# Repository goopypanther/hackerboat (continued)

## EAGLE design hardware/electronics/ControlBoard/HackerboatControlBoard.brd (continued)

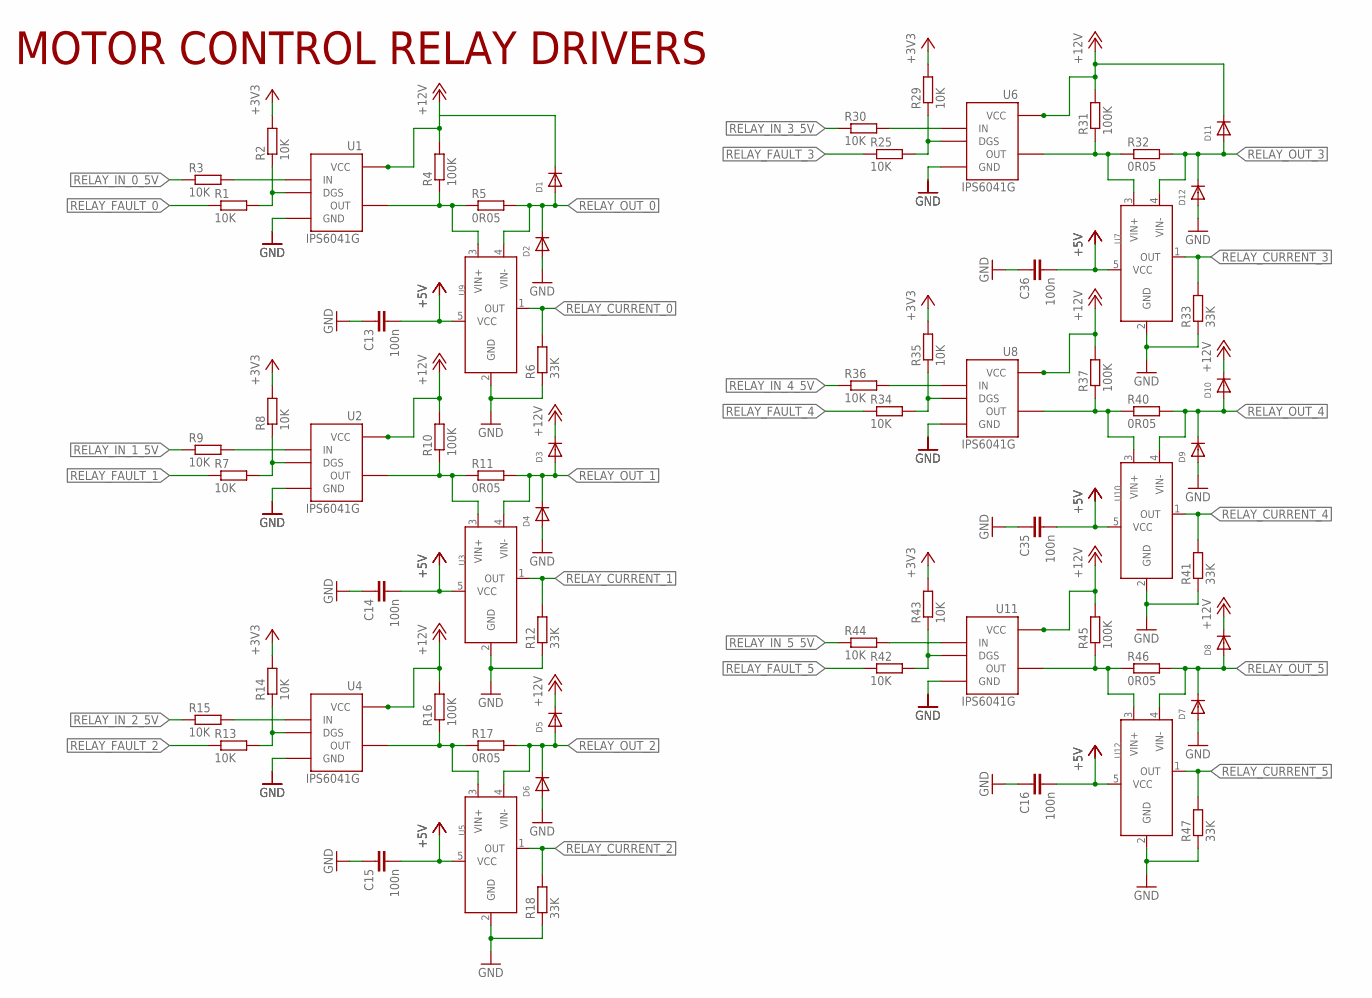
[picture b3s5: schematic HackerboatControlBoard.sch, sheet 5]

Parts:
C13, C14, C15, C16, C35, C36: 100n; C0603; PARTNO CC0603KRX7R9BB104
D1, D2, D3, D4, D5, D6, D7, D8, D9, D10, D11, D12: DIODESOD-123; SOD-123; PARTNO CDBW140-G
R1, R2, R3, R7, R8, R9, R13, R14, R15, R25, R29, R30, R34, R35, R36, R42, R43, R44: 10K; R0603; PARTNO RNCP0603FTD10K0
R4, R10, R16, R31, R37, R45: 100K; R0603; PARTNO CRCW0603100KFKEA
R5, R11, R17, R32, R40, R46: 0R05; R2512; PARTNO PE2512FKE070R05L
R6, R12, R18, R33, R41, R47: 33K; R0603; PARTNO ERJ-3EKF3302V
U1, U2, U4, U6, U8, U11: IPS6041G; SO08; PARTNO IPS6041GPBF
U3, U5, U7, U9, U10, U12: INA169; SOT23-5L; PARTNO INA169NA/3K

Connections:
+3V3: R2.2, R8.2, R14.2, R29.2, R35.2, R43.2; also elsewhere on the board
+5V: C13.2, C14.2, C15.2, C16.2, C35.2, C36.2, U3.5 (VCC), U5.5 (VCC), U7.5 (VCC), U9.5 (VCC), U10.5 (VCC), U12.5 (VCC); also elsewhere on the board
+12V: D1.C, D3.C, D5.C, D8.C, D10.C, D11.C, R4.2, R10.2, R16.2, R31.2, R37.2, R45.2, U1.5 (VCC), U1.6 (VCC), U1.7 (VCC), U1.8 (VCC), U2.5 (VCC), U2.6 (VCC), U2.7 (VCC), U2.8 (VCC), U4.5 (VCC), U4.6 (VCC), U4.7 (VCC), U4.8 (VCC), U6.5 (VCC), U6.6 (VCC), U6.7 (VCC), U6.8 (VCC), U8.5 (VCC), U8.6 (VCC), U8.7 (VCC), U8.8 (VCC), U11.5 (VCC), U11.6 (VCC), U11.7 (VCC), U11.8 (VCC); also elsewhere on the board
GND: C13.1, C14.1, C15.1, C16.1, C35.1, C36.1, D2.A, D4.A, D6.A, D7.A, D9.A, D12.A, R6.1, R12.1, R18.1, R33.1, R41.1, R47.1, U1.1 (GND), U2.1 (GND), U3.2 (GND), U4.1 (GND), U5.2 (GND), U6.1 (GND), U7.2 (GND), U8.1 (GND), U9.2 (GND), U10.2 (GND), U11.1 (GND), U12.2 (GND); also elsewhere on the board
unnamed: R1.2, R2.1, U1.3 (DGS)
unnamed: R3.2, U1.2 (IN)
unnamed: R4.1, R5.1, U1.4 (OUT), U9.3 (VIN+)
unnamed: R7.2, R8.1, U2.3 (DGS)
unnamed: R9.2, U2.2 (IN)
unnamed: R10.1, R11.1, U2.4 (OUT), U3.3 (VIN+)
unnamed: R13.2, R14.1, U4.3 (DGS)
unnamed: R15.2, U4.2 (IN)
unnamed: R16.1, R17.1, U4.4 (OUT), U5.3 (VIN+)
unnamed: R25.2, R29.1, U6.3 (DGS)
unnamed: R30.2, U6.2 (IN)
unnamed: R31.1, R32.1, U6.4 (OUT), U7.3 (VIN+)
unnamed: R34.2, R35.1, U8.3 (DGS)
unnamed: R36.2, U8.2 (IN)
unnamed: R37.1, R40.1, U8.4 (OUT), U10.3 (VIN+)
unnamed: R42.2, R43.1, U11.3 (DGS)
unnamed: R44.2, U11.2 (IN)
unnamed: R45.1, R46.1, U11.4 (OUT), U12.3 (VIN+)
RELAY_CURRENT_0: R6.2, U9.1 (OUT); also elsewhere on the board
RELAY_CURRENT_1: R12.2, U3.1 (OUT); also elsewhere on the board
RELAY_CURRENT_2: R18.2, U5.1 (OUT); also elsewhere on the board
RELAY_CURRENT_3: R33.2, U7.1 (OUT); also elsewhere on the board
RELAY_CURRENT_4: R41.2, U10.1 (OUT); also elsewhere on the board
RELAY_CURRENT_5: R47.2, U12.1 (OUT); also elsewhere on the board
RELAY_FAULT_0: R1.1; also elsewhere on the board
RELAY_FAULT_1: R7.1; also elsewhere on the board
RELAY_FAULT_2: R13.1; also elsewhere on the board
RELAY_FAULT_3: R25.1; also elsewhere on the board
RELAY_FAULT_4: R34.1; also elsewhere on the board
RELAY_FAULT_5: R42.1; also elsewhere on the board
RELAY_IN_0_5V: R3.1; also elsewhere on the board
RELAY_IN_1_5V: R9.1; also elsewhere on the board
RELAY_IN_2_5V: R15.1; also elsewhere on the board
RELAY_IN_3_5V: R30.1; also elsewhere on the board
RELAY_IN_4_5V: R36.1; also elsewhere on the board
RELAY_IN_5_5V: R44.1; also elsewhere on the board
RELAY_OUT_0: D1.A, D2.C, R5.2, U9.4 (VIN-); also elsewhere on the board
RELAY_OUT_1: D3.A, D4.C, R11.2, U3.4 (VIN-); also elsewhere on the board
RELAY_OUT_2: D5.A, D6.C, R17.2, U5.4 (VIN-); also elsewhere on the board
RELAY_OUT_3: D11.A, D12.C, R32.2, U7.4 (VIN-); also elsewhere on the board
RELAY_OUT_4: D9.C, D10.A, R40.2, U10.4 (VIN-); also elsewhere on the board
RELAY_OUT_5: D7.C, D8.A, R46.2, U12.4 (VIN-); also elsewhere on the board

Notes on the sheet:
MOTOR CONTROL RELAY DRIVERS

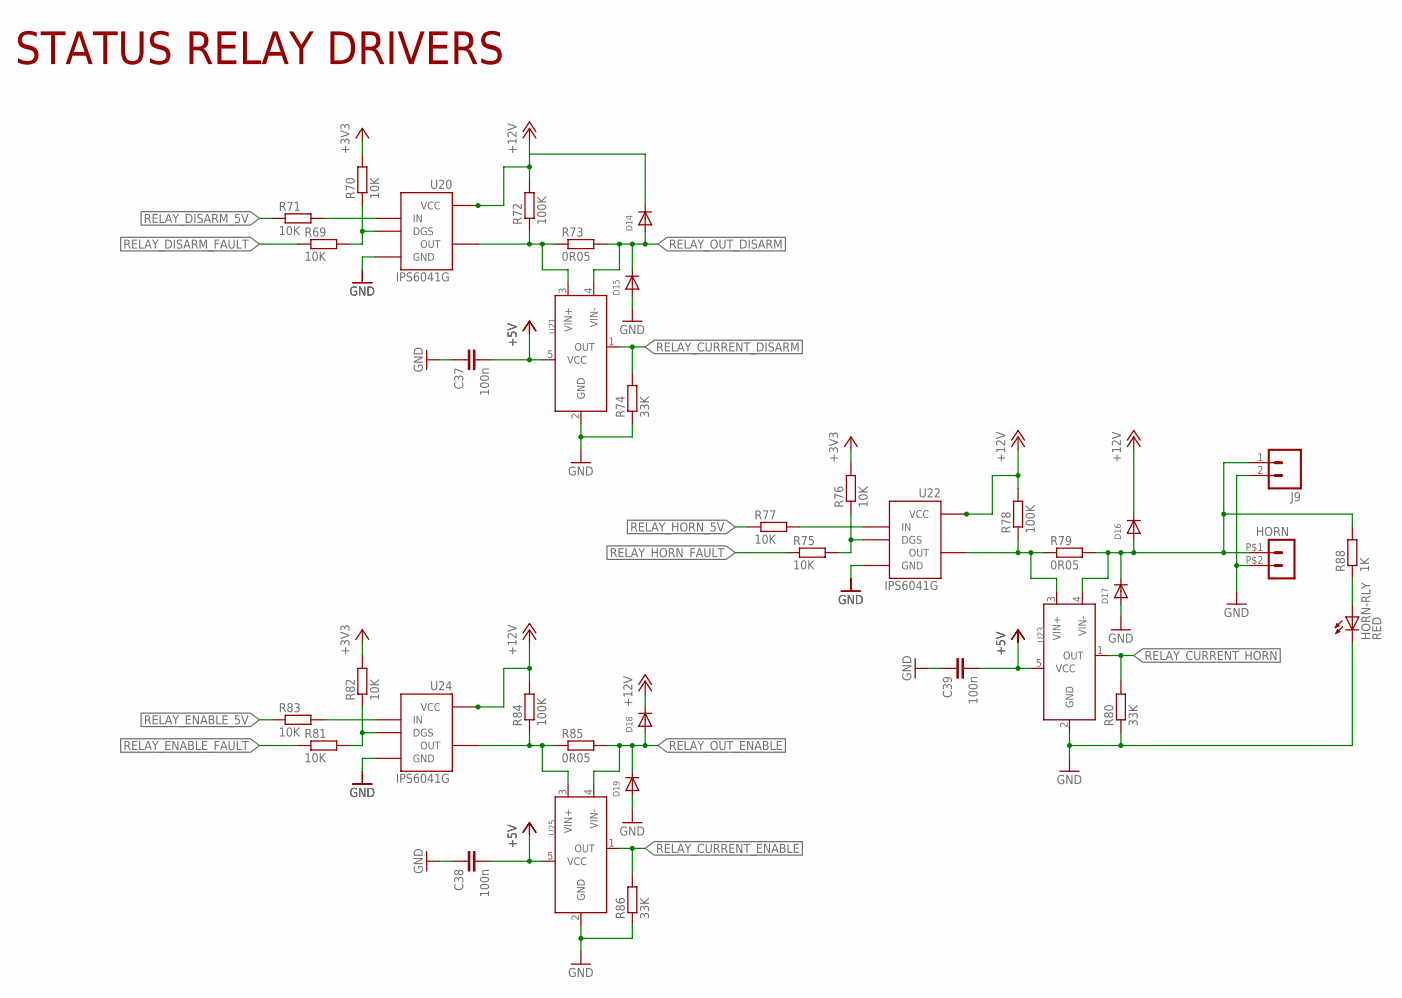
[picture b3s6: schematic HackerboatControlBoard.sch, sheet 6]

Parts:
C37, C38, C39: 100n; C0603; PARTNO CC0603KRX7R9BB104
D14, D15, D16, D17, D18, D19: DIODESOD-123; SOD-123; PARTNO CDBW140-G
HORN: HEADER_POS2_70555; 70555-POS2; PARTNO 0705550036
HORN-RLY: RED; CHIPLED_0805; PARTNO LH R974-LP-1
J9: M02LOCK; 1X02_LOCK; PARTNO ?
R69, R70, R71, R75, R76, R77, R81, R82, R83: 10K; R0603; PARTNO RNCP0603FTD10K0
R72, R78, R84: 100K; R0603; PARTNO CRCW0603100KFKEA
R73, R79, R85: 0R05; R2512; PARTNO PE2512FKE070R05L
R74, R80, R86: 33K; R0603; PARTNO ERJ-3EKF3302V
R88: 1K; R0603; PARTNO RMCF0603FT1K00
U20, U22, U24: IPS6041G; SO08; PARTNO IPS6041GPBF
U21, U23, U25: INA169; SOT23-5L; PARTNO INA169NA/3K

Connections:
+3V3: R70.2, R76.2, R82.2; also elsewhere on the board
+5V: C37.2, C38.2, C39.2, U21.5 (VCC), U23.5 (VCC), U25.5 (VCC); also elsewhere on the board
+12V: D14.C, D16.C, D18.C, R72.2, R78.2, R84.2, U20.5 (VCC), U20.6 (VCC), U20.7 (VCC), U20.8 (VCC), U22.5 (VCC), U22.6 (VCC), U22.7 (VCC), U22.8 (VCC), U24.5 (VCC), U24.6 (VCC), U24.7 (VCC), U24.8 (VCC); also elsewhere on the board
GND: C37.1, C38.1, C39.1, D15.A, D17.A, D19.A, HORN.P$2 (2), HORN-RLY.C, J9.2, R74.1, R80.1, R86.1, U20.1 (GND), U21.2 (GND), U22.1 (GND), U23.2 (GND), U24.1 (GND), U25.2 (GND); also elsewhere on the board
unnamed: R69.2, R70.1, U20.3 (DGS)
unnamed: R71.2, U20.2 (IN)
unnamed: R72.1, R73.1, U20.4 (OUT), U21.3 (VIN+)
unnamed: R75.2, R76.1, U22.3 (DGS)
unnamed: R77.2, U22.2 (IN)
unnamed: R78.1, R79.1, U22.4 (OUT), U23.3 (VIN+)
unnamed: R81.2, R82.1, U24.3 (DGS)
unnamed: R83.2, U24.2 (IN)
unnamed: R84.1, R85.1, U24.4 (OUT), U25.3 (VIN+)
unnamed: HORN-RLY.A, R88.1
RELAY_CURRENT_DISARM: R74.2, U21.1 (OUT); also elsewhere on the board
RELAY_CURRENT_ENABLE: R86.2, U25.1 (OUT); also elsewhere on the board
RELAY_CURRENT_HORN: R80.2, U23.1 (OUT); also elsewhere on the board
RELAY_DISARM_5V: R71.1; also elsewhere on the board
RELAY_DISARM_FAULT: R69.1; also elsewhere on the board
RELAY_ENABLE_5V: R83.1; also elsewhere on the board
RELAY_ENABLE_FAULT: R81.1; also elsewhere on the board
RELAY_HORN_5V: R77.1; also elsewhere on the board
RELAY_HORN_FAULT: R75.1; also elsewhere on the board
RELAY_OUT_DISARM: D14.A, D15.C, R73.2, U21.4 (VIN-); also elsewhere on the board
RELAY_OUT_ENABLE: D18.A, D19.C, R85.2, U25.4 (VIN-); also elsewhere on the board
RELAY_OUT_HORN: D16.A, D17.C, HORN.P$1 (1), J9.1, R79.2, R88.2, U23.4 (VIN-)

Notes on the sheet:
STATUS RELAY DRIVERS

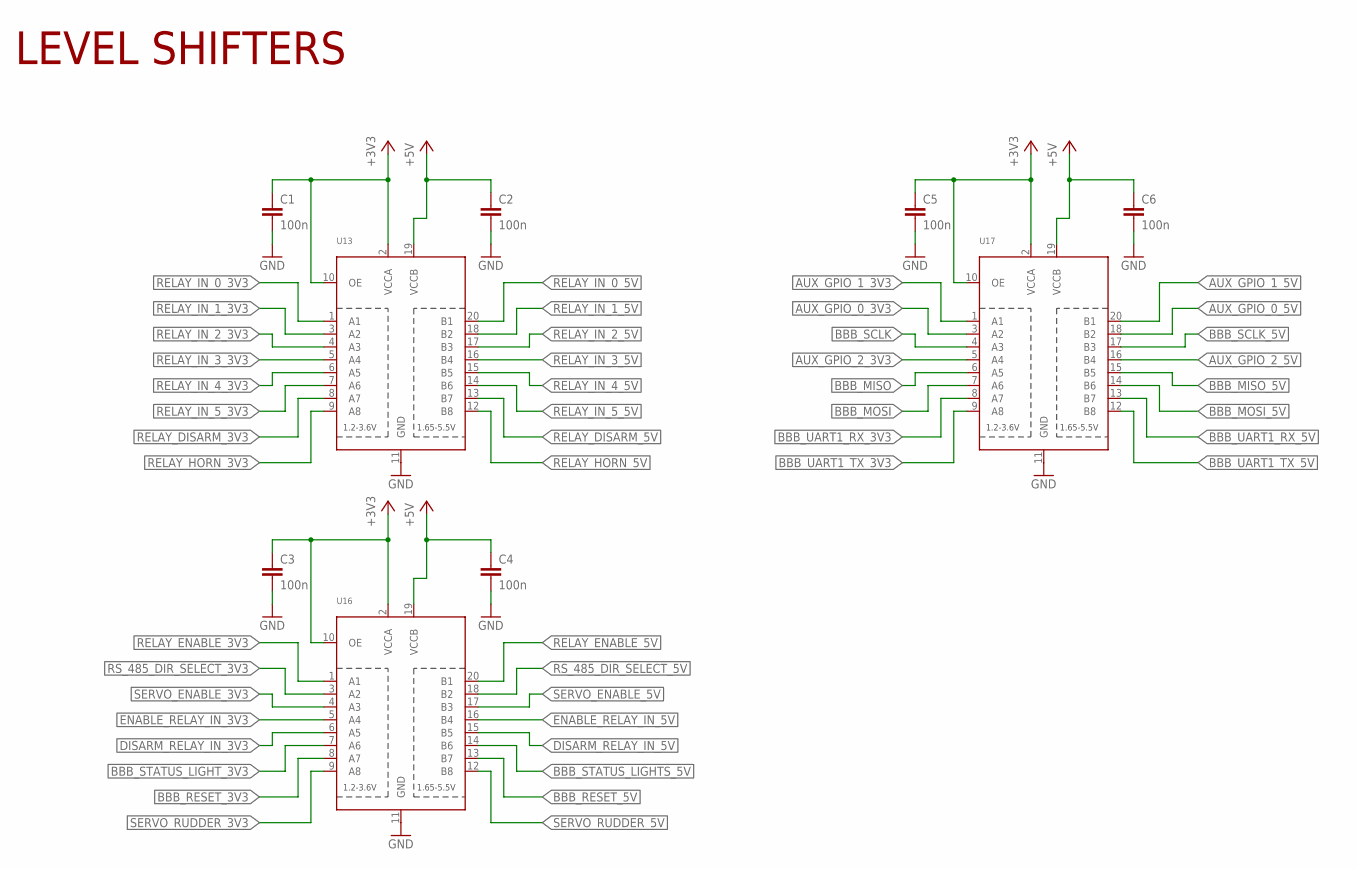
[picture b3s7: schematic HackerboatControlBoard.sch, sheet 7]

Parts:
C1, C2, C3, C4, C5, C6: 100n; C0603; PARTNO CC0603KRX7R9BB104
U13, U16, U17: TXB0108PWR; TSSOP20; PARTNO TXB0108PWR

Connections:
+3V3: C1.1, C3.1, C5.1, U13.2 (VCCA), U13.10 (OE), U16.2 (VCCA), U16.10 (OE), U17.2 (VCCA), U17.10 (OE); also elsewhere on the board
+5V: C2.1, C4.1, C6.1, U13.19 (VCCB), U16.19 (VCCB), U17.19 (VCCB); also elsewhere on the board
AUX_GPIO_0_3V3: U17.3 (A2); also elsewhere on the board
AUX_GPIO_0_5V: U17.18 (B2); also elsewhere on the board
AUX_GPIO_1_3V3: U17.1 (A1); also elsewhere on the board
AUX_GPIO_1_5V: U17.20 (B1); also elsewhere on the board
AUX_GPIO_2_3V3: U17.5 (A4); also elsewhere on the board
AUX_GPIO_2_5V: U17.16 (B4); also elsewhere on the board
BBB_MISO: U17.6 (A5); also elsewhere on the board
BBB_MISO_5V: U17.15 (B5); also elsewhere on the board
BBB_MOSI: U17.7 (A6); also elsewhere on the board
BBB_MOSI_5V: U17.14 (B6); also elsewhere on the board
BBB_RESET_3V3: U16.8 (A7); also elsewhere on the board
BBB_RESET_5V: U16.13 (B7); also elsewhere on the board
BBB_SCLK: U17.4 (A3); also elsewhere on the board
BBB_SCLK_5V: U17.17 (B3); also elsewhere on the board
BBB_STATUS_LIGHTS_5V: U16.14 (B6); also elsewhere on the board
BBB_STATUS_LIGHT_3V3: U16.7 (A6)
BBB_UART1_RX_3V3: U17.8 (A7); also elsewhere on the board
BBB_UART1_RX_5V: U17.13 (B7); also elsewhere on the board
BBB_UART1_TX_3V3: U17.9 (A8); also elsewhere on the board
BBB_UART1_TX_5V: U17.12 (B8); also elsewhere on the board
DISARM_RELAY_IN_3V3: U16.6 (A5); also elsewhere on the board
DISARM_RELAY_IN_5V: U16.15 (B5); also elsewhere on the board
ENABLE_RELAY_IN_3V3: U16.5 (A4); also elsewhere on the board
ENABLE_RELAY_IN_5V: U16.16 (B4); also elsewhere on the board
GND: C1.2, C2.2, C3.2, C4.2, C5.2, C6.2, U13.11 (GND), U16.11 (GND), U17.11 (GND); also elsewhere on the board
RELAY_DISARM_3V3: U13.8 (A7); also elsewhere on the board
RELAY_DISARM_5V: U13.13 (B7); also elsewhere on the board
RELAY_ENABLE_3V3: U16.1 (A1); also elsewhere on the board
RELAY_ENABLE_5V: U16.20 (B1); also elsewhere on the board
RELAY_HORN_3V3: U13.9 (A8); also elsewhere on the board
RELAY_HORN_5V: U13.12 (B8); also elsewhere on the board
RELAY_IN_0_3V3: U13.1 (A1); also elsewhere on the board
RELAY_IN_0_5V: U13.20 (B1); also elsewhere on the board
RELAY_IN_1_3V3: U13.3 (A2); also elsewhere on the board
RELAY_IN_1_5V: U13.18 (B2); also elsewhere on the board
RELAY_IN_2_3V3: U13.4 (A3); also elsewhere on the board
RELAY_IN_2_5V: U13.17 (B3); also elsewhere on the board
RELAY_IN_3_3V3: U13.5 (A4); also elsewhere on the board
RELAY_IN_3_5V: U13.16 (B4); also elsewhere on the board
RELAY_IN_4_3V3: U13.6 (A5); also elsewhere on the board
RELAY_IN_4_5V: U13.15 (B5); also elsewhere on the board
RELAY_IN_5_3V3: U13.7 (A6); also elsewhere on the board
RELAY_IN_5_5V: U13.14 (B6); also elsewhere on the board
RS_485_DIR_SELECT_3V3: U16.3 (A2); also elsewhere on the board
RS_485_DIR_SELECT_5V: U16.18 (B2); also elsewhere on the board
SERVO_ENABLE_3V3: U16.4 (A3); also elsewhere on the board
SERVO_ENABLE_5V: U16.17 (B3); also elsewhere on the board
SERVO_RUDDER_3V3: U16.9 (A8); also elsewhere on the board
SERVO_RUDDER_5V: U16.12 (B8); also elsewhere on the board

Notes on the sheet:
LEVEL SHIFTERS

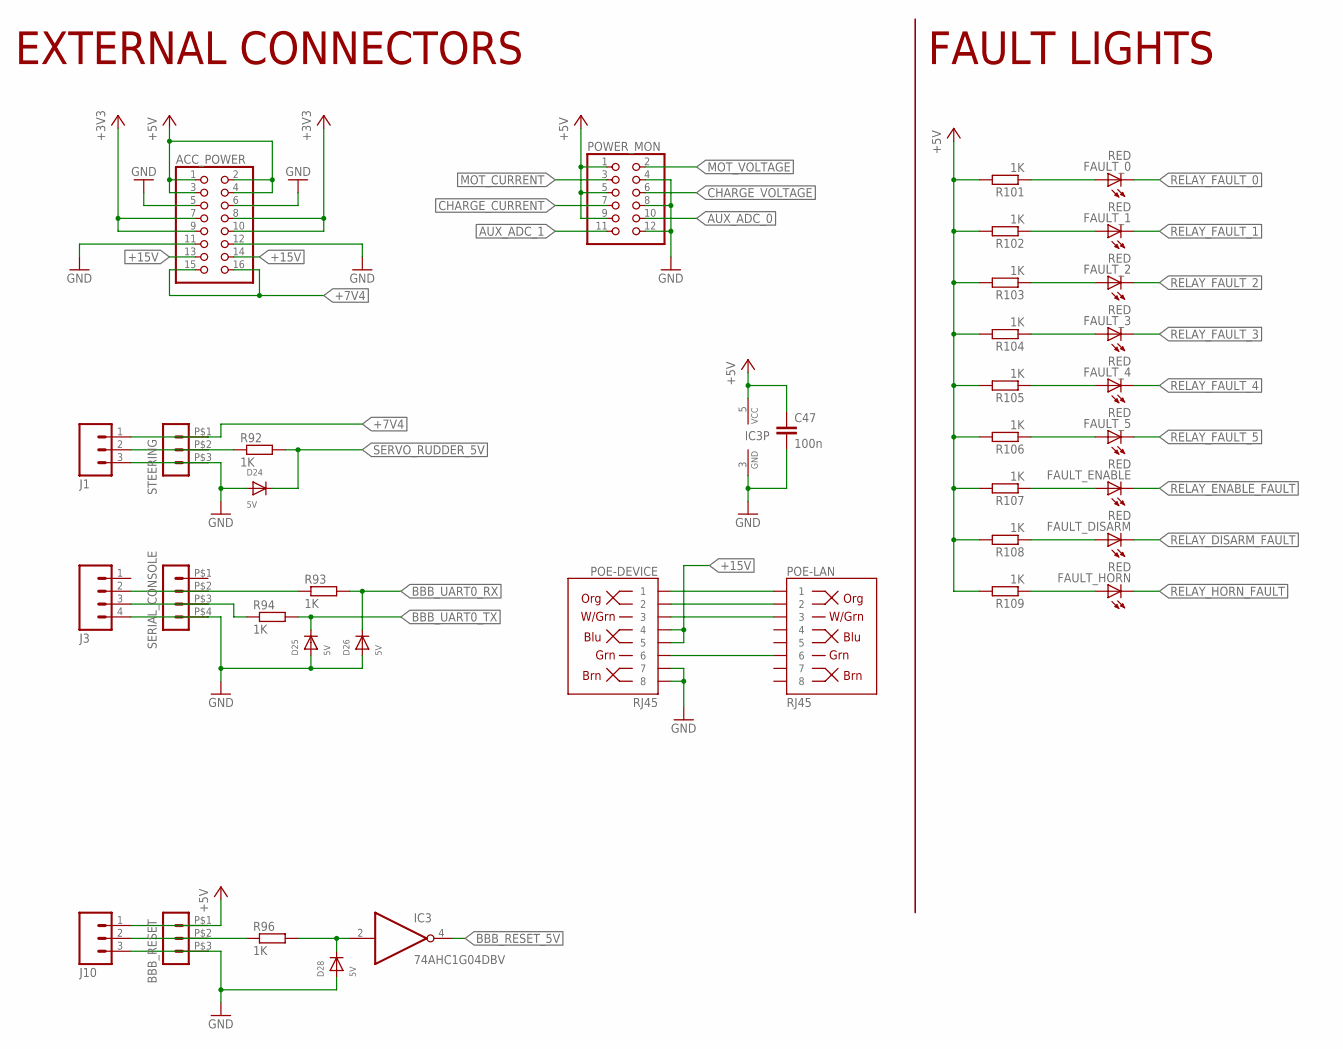
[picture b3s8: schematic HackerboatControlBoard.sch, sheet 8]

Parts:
ACC_POWER: PINHD-2X8_2.54; 2X08; PARTNO *
BBB_RESET: HEADER_POS3_70555; 70555-POS3; PARTNO 0705550037
C47: 100n; C0603; PARTNO CC0603KRX7R9BB104
D24, D25, D26, D28: 5V; SOD-123; PARTNO SMF5.0A
FAULT_0, FAULT_1, FAULT_2, FAULT_3, FAULT_4, FAULT_5: RED; CHIPLED_0805; PARTNO LH R974-LP-1
FAULT_DISARM: RED; CHIPLED_0805; PARTNO LH R974-LP-1
FAULT_ENABLE: RED; CHIPLED_0805; PARTNO LH R974-LP-1
FAULT_HORN: RED; CHIPLED_0805; PARTNO LH R974-LP-1
IC3: 74AHC1G04DBV; SOT23-5; PARTNO MC74HC1G04DTT1G
J1, J10: M03LOCK; 1X03_LOCK; PARTNO ?
J3: M04LOCK; 1X04_LOCK; PARTNO *
POE-DEVICE: RJ45; RJ45-8; PARTNO 615008137121
POE-LAN: RJ45; RJ45-8; PARTNO 615008137121
POWER_MON: PINHD-2X6_2.54; 2X06; PARTNO *
R92, R93, R94, R96, R101, R102, R103, R104, R105, R106, R107, R108, R109: 1K; R0603; PARTNO RMCF0603FT1K00
SERIAL_CONSOLE: HEADER_POS4_70555; 70555-POS4; PARTNO 0705550038
STEERING: HEADER_POS3_70555; 70555-POS3; PARTNO 0705550037

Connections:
+3V3: ACC_POWER.7, ACC_POWER.8, ACC_POWER.9, ACC_POWER.10; also elsewhere on the board
+5V: ACC_POWER.1, ACC_POWER.2, ACC_POWER.3, ACC_POWER.4, BBB_RESET.P$1 (1), C47.1, IC3.5 (VCC), J10.1, POWER_MON.1, POWER_MON.5, POWER_MON.9, R101.2, R102.2, R103.2, R104.2, R105.2, R106.2, R107.2, R108.2, R109.2; also elsewhere on the board
+7V4: ACC_POWER.15, ACC_POWER.16, J1.1, STEERING.P$1 (1); also elsewhere on the board
+15V: ACC_POWER.13, ACC_POWER.14, POE-DEVICE.4, POE-DEVICE.5; also elsewhere on the board
AUX_ADC_0: POWER_MON.10; also elsewhere on the board
AUX_ADC_1: POWER_MON.11; also elsewhere on the board
BBB_RESET_5V: IC3.4 (O); also elsewhere on the board
BBB_UART0_RX: D26.C, R93.2; also elsewhere on the board
BBB_UART0_TX: D25.C, R94.2; also elsewhere on the board
CHARGE_CURRENT: POWER_MON.7; also elsewhere on the board
CHARGE_VOLTAGE: POWER_MON.6; also elsewhere on the board
GND: ACC_POWER.5, ACC_POWER.6, ACC_POWER.11, ACC_POWER.12, BBB_RESET.P$3 (3), C47.2, D24.A, D25.A, D26.A, D28.A, IC3.3 (GND), J1.3, J3.4, J10.3, POE-DEVICE.7, POE-DEVICE.8, POWER_MON.4, POWER_MON.8, POWER_MON.12, SERIAL_CONSOLE.P$4 (4), STEERING.P$3 (3); also elsewhere on the board
MOT_CURRENT: POWER_MON.3; also elsewhere on the board
MOT_VOLTAGE: POWER_MON.2; also elsewhere on the board
unnamed: D28.C, IC3.2 (I), R96.2
unnamed: POE-DEVICE.1, POE-LAN.1
unnamed: POE-DEVICE.2, POE-LAN.2
unnamed: POE-DEVICE.3, POE-LAN.3
unnamed: POE-DEVICE.6, POE-LAN.6
unnamed: J1.2, R92.1, STEERING.P$2 (2)
unnamed: J3.2, R93.1, SERIAL_CONSOLE.P$2 (2)
unnamed: J3.3, R94.1, SERIAL_CONSOLE.P$3 (3)
unnamed: BBB_RESET.P$2 (2), J10.2, R96.1
unnamed: FAULT_0.A, R101.1
unnamed: FAULT_1.A, R102.1
unnamed: FAULT_2.A, R103.1
unnamed: FAULT_3.A, R104.1
unnamed: FAULT_4.A, R105.1
unnamed: FAULT_5.A, R106.1
unnamed: FAULT_ENABLE.A, R107.1
unnamed: FAULT_DISARM.A, R108.1
unnamed: FAULT_HORN.A, R109.1
RELAY_DISARM_FAULT: FAULT_DISARM.C; also elsewhere on the board
RELAY_ENABLE_FAULT: FAULT_ENABLE.C; also elsewhere on the board
RELAY_FAULT_0: FAULT_0.C; also elsewhere on the board
RELAY_FAULT_1: FAULT_1.C; also elsewhere on the board
RELAY_FAULT_2: FAULT_2.C; also elsewhere on the board
RELAY_FAULT_3: FAULT_3.C; also elsewhere on the board
RELAY_FAULT_4: FAULT_4.C; also elsewhere on the board
RELAY_FAULT_5: FAULT_5.C; also elsewhere on the board
RELAY_HORN_FAULT: FAULT_HORN.C; also elsewhere on the board
SERVO_RUDDER_5V: D24.C, R92.2; also elsewhere on the board

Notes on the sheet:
EXTERNAL CONNECTORS
FAULT LIGHTS

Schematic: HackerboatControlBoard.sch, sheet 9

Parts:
C19: 10u; C1210; PARTNO UMK325BJ106MM
C20: 22u; C1210; PARTNO GRM32ER61E226KE15K
CELL: FONA; FONA-3G; PARTNO BCS-118-L-S-TE
D27: 5V; SOD-123; PARTNO SMF5.0A
F2: PTC-2920; 2920L; PARTNO MF-LSMF300/24X-2
GPS: ULTIMATE-GPS; PARTNO BCS-109-L-S-TE
IC5: V7805-2000; TO220V; PARTNO V7805-2000
IMU: 9-DOF-BREAKOUT; PARTNO BCS-110-L-S-TE
J2: M03LOCK; 1X03_LOCK; PARTNO ?
J5: M09LOCK; 1X09_LOCK; PARTNO *
J6: M10LOCK; 1X10_LOCK; PARTNO *
J7: M18_; 1X18; PARTNO *
R19: 4K7'; R0603; PARTNO RC1608J472CS
R20: 4K7; R0603; PARTNO RC1608J472CS
R95: 1K; R0603; PARTNO RMCF0603FT1K00
STATUS_LIGHTS: HEADER_POS3_70555; 70555-POS3; PARTNO 0705550037

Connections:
+3V3: CELL.VIO (15), J7.15, R19.2, R20.2; also elsewhere on the board
+5V: CELL.5V (18), GPS.VIN (5), IMU.VIN (1), J5.2, J6.1, J7.18; also elsewhere on the board
+12V: C19.1, IC5.1 (VI); also elsewhere on the board
BBB_I2C_1_SCL: IMU.SCL (4), J6.4, R19.1; also elsewhere on the board
BBB_I2C_1_SDA: IMU.SDA (5), J6.5, R20.1; also elsewhere on the board
BBB_STATUS_LIGHTS_5V: D27.C, R95.2; also elsewhere on the board
CELL_CTS: CELL.CTS (9), J7.9; also elsewhere on the board
CELL_KEY: CELL.KEY (8), J7.8; also elsewhere on the board
CELL_NET_STATUS: CELL.NS (5), J7.5; also elsewhere on the board
CELL_POWER_STATUS: CELL.PS (6), J7.6; also elsewhere on the board
CELL_RESET: CELL.RST (14), J7.14; also elsewhere on the board
CELL_RING: CELL.RI (7), J7.7; also elsewhere on the board
CELL_RTS: CELL.RTS (11), J7.11; also elsewhere on the board
CELL_RX: CELL.RX (13), J7.13; also elsewhere on the board
CELL_TX: CELL.TX (12), J7.12; also elsewhere on the board
GND: C19.2, C20.2, CELL.GND (16), D27.A, GPS.GND (6), IC5.2 (GND), IMU.GND (3), J2.3, J5.3, J6.3, J7.16, STATUS_LIGHTS.P$3 (3); also elsewhere on the board
GNSS_ENABLE: GPS.EN (8), J5.8; also elsewhere on the board
GNSS_FIX: GPS.FIX (7), J5.6; also elsewhere on the board
GNSS_RX: GPS.RX (2), J5.4; also elsewhere on the board
GNSS_TX: GPS.TX (3), J5.5; also elsewhere on the board
unnamed: GPS.PPS (1), J5.1
unnamed: GPS.VBAT (4), J5.7
unnamed: IMU.3VO (2), J6.2
unnamed: IMU.GINT (6), J6.6
unnamed: IMU.GRDY (7), J6.7
unnamed: IMU.LIN1 (8), J6.8
unnamed: IMU.LIN2 (9), J6.9
unnamed: IMU.LRDY (10), J6.10
unnamed: GPS.3V3 (9), J5.9
unnamed: CELL.SPKR+ (2), J7.2
unnamed: CELL.MIC- (3), J7.3
unnamed: CELL.MIC+ (4), J7.4
unnamed: CELL.DTR (10), J7.10
unnamed: CELL.BAT (17), J7.17
unnamed: CELL.SPKR- (1), J7.1
unnamed: F2.P$1 (1), J2.1, STATUS_LIGHTS.P$1 (1)
unnamed: C20.1, F2.P$2 (2), IC5.3 (VO)
unnamed: J2.2, R95.1, STATUS_LIGHTS.P$2 (2)

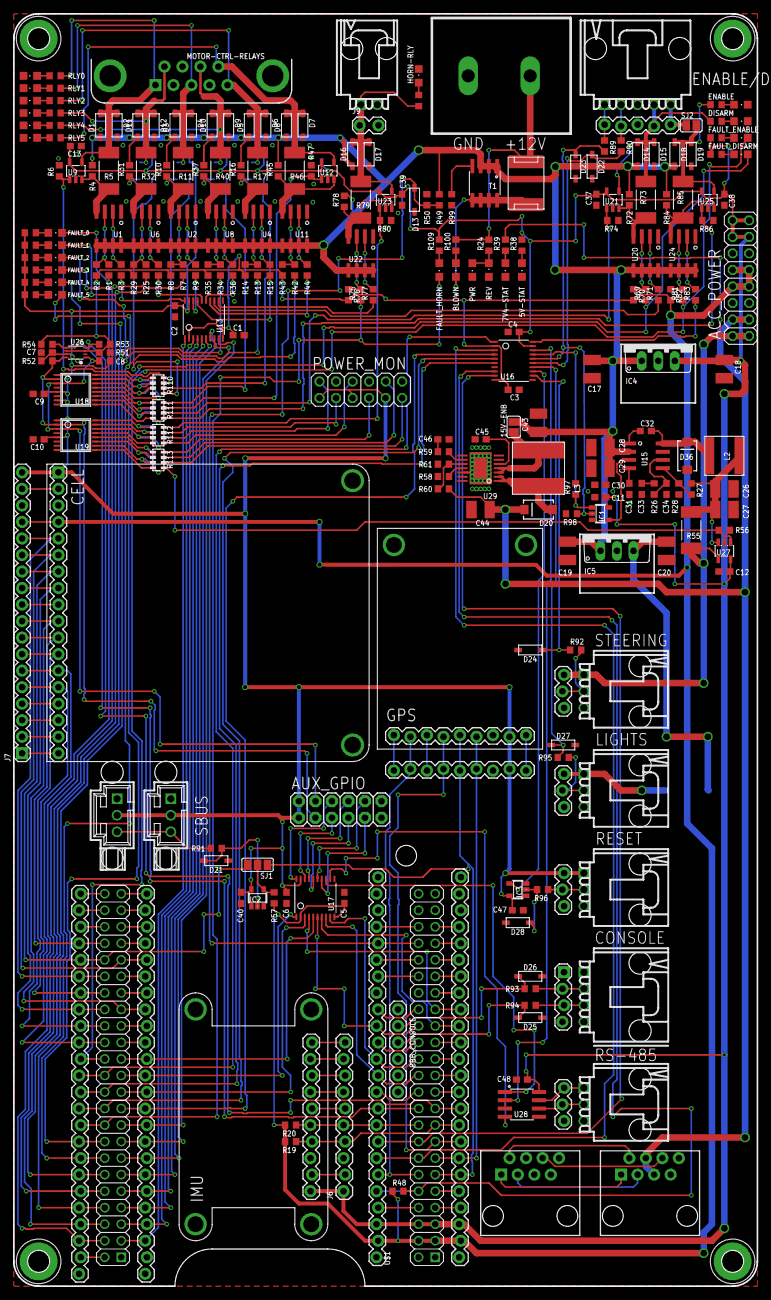
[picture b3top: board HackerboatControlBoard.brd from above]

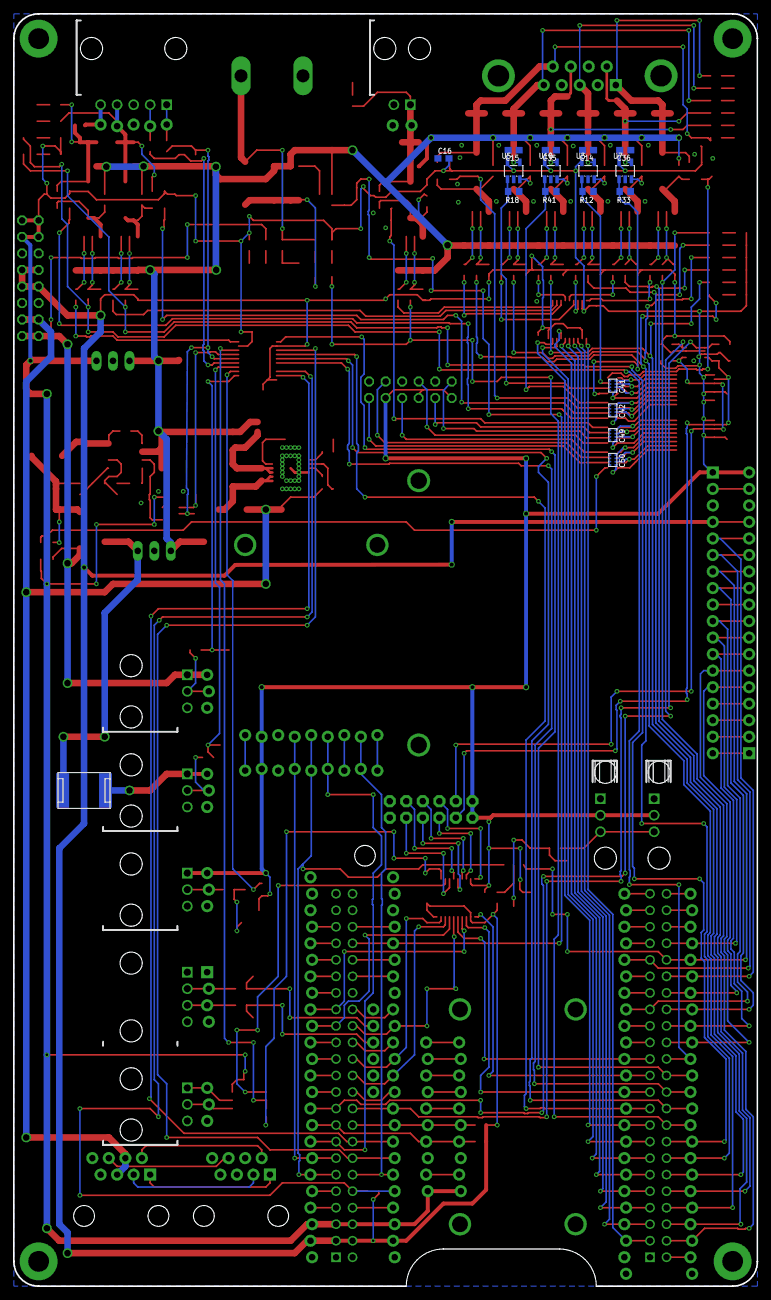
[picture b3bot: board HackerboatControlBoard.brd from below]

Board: 2 copper layers, 114.3 x 195.6 mm, 287 parts (18 on the bottom side), 256 nets.

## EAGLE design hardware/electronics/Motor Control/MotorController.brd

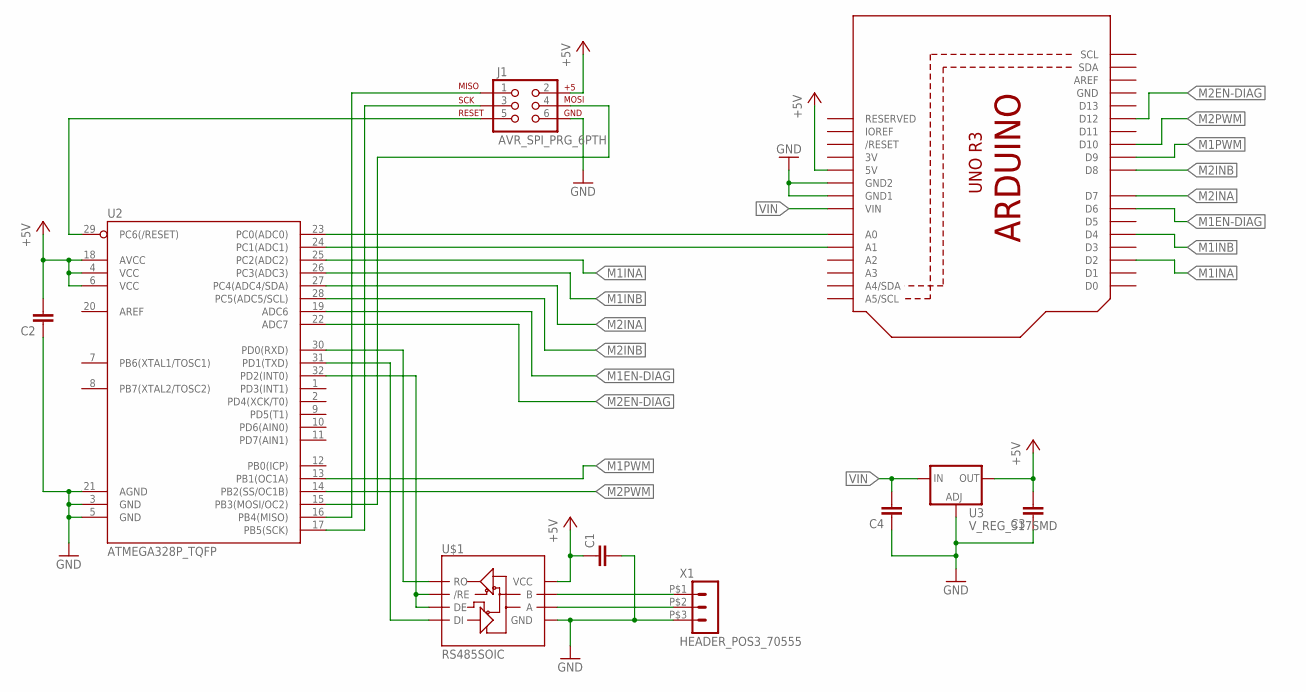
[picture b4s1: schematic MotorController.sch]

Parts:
C1, C2: C-EUC0603; C0603
C3, C4: C-EUC1206; C1206
J1: AVR_SPI_PRG_6PTH; 2X3
U1: ARDUINOR3-BPLACE
U2: ATMEGA328P_TQFP; TQFP32-08
U3: V_REG_317SMD; SOT223
U$1: RS485SOIC; SO08
X1: HEADER_POS3_70555; 70555-POS3

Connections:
3V: U1.3V
+5V: C1.1, C2.2, C3.2, J1.2, U1.5V, U2.4 (VCC), U2.6 (VCC), U2.18 (AVCC), U3.2 (OUT), U$1.8 (VCC)
GND: C1.2, C2.1, C3.1, C4.1, J1.6, U1.GND, U1.GND1, U1.GND2, U2.3 (GND), U2.5 (GND), U2.21 (AGND), U3.1 (ADJ), U$1.5 (GND), X1.P$3 (3)
M1EN-DIAG: U1.D6, U2.19 (ADC6)
M1INA: U1.D2, U2.25 (PC2(ADC2))
M1INB: U1.D4, U2.26 (PC3(ADC3))
M1PWM: U1.D9, U2.13 (PB1(OC1A))
M2EN-DIAG: U1.D12, U2.22 (ADC7)
M2INA: U1.D7, U2.27 (PC4(ADC4/SDA))
M2INB: U1.D8, U2.28 (PC5(ADC5/SCL))
M2PWM: U1.D10, U2.14 (PB2(SS/OC1B))
unnamed: J1.5, U2.29 (PC6(/RESET))
unnamed: J1.3, U2.17 (PB5(SCK))
unnamed: J1.1, U2.16 (PB4(MISO))
unnamed: J1.4, U2.15 (PB3(MOSI/OC2))
unnamed: U2.32 (PD2(INT0)), U$1.2 (/RE), U$1.3 (DE)
unnamed: U2.30 (PD0(RXD)), U$1.1 (RO)
unnamed: U2.31 (PD1(TXD)), U$1.4 (DI)
unnamed: U1.A0, U2.23 (PC0(ADC0))
unnamed: U1.A1, U2.24 (PC1(ADC1))
unnamed: U$1.7 (B), X1.P$1 (1)
unnamed: U$1.6 (A), X1.P$2 (2)
VIN: C4.2, U1.VIN, U3.3 (IN)

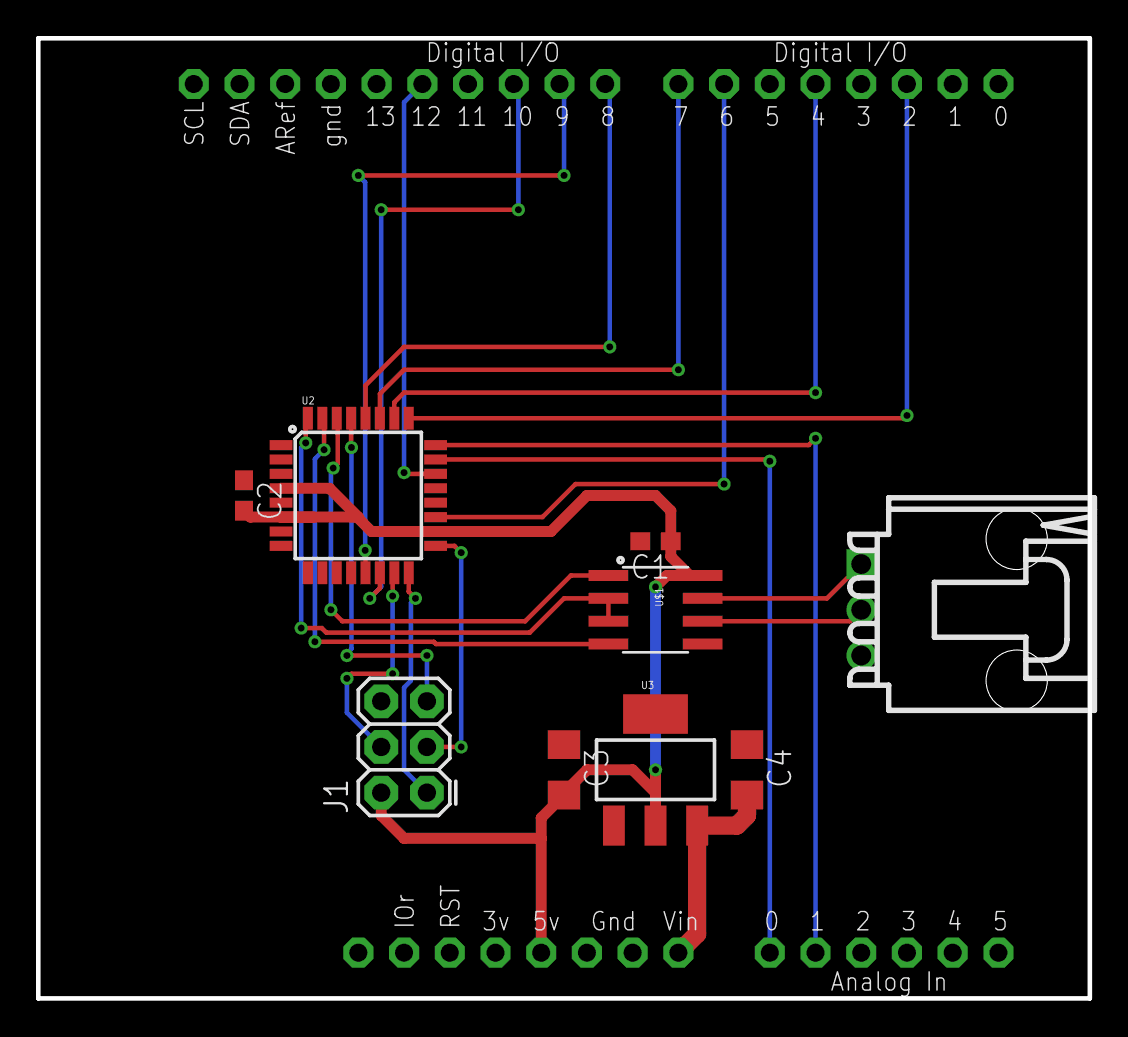
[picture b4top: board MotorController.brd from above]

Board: 2 copper layers, 58.4 x 53.3 mm, 10 parts (0 on the bottom side), 22 nets.

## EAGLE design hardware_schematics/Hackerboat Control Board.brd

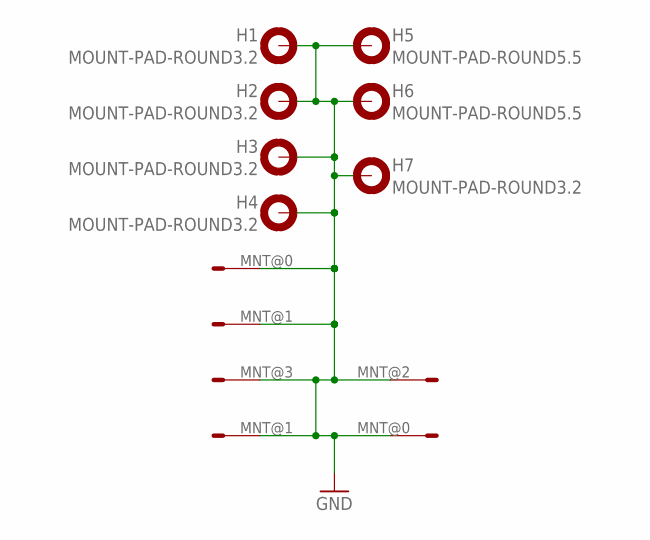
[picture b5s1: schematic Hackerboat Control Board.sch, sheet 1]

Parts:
GPS: ULTIMATE-GPS
H1, H2, H3, H4, H7: MOUNT-PAD-ROUND3.2; 3,2-PAD
H5, H6: MOUNT-PAD-ROUND5.5; 5,5-PAD
IMU: 9-DOF-BREAKOUT

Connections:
GND: GPS.MNT@0 (9), GPS.MNT@1 (9), H1.B3,2, H2.B3,2, H3.B3,2, H4.B3,2, H5.B5,5, H6.B5,5, H7.B3,2, IMU.MNT@0 (9), IMU.MNT@1 (9), IMU.MNT@2 (9), IMU.MNT@3 (9); also elsewhere on the board
